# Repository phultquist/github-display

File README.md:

# GitHub Display

An ESP32-powered LED matrix display that shows your GitHub contribution graph in real-time.

## Features

- 256 LED (16x16) matrix display
- Automatic WiFi connection with captive portal setup
- Fetches data from custom API every 10 seconds
- Hard-coded Device ID: "1"
- WiFi credential reset functionality

## Initial Setup

### First Time Power-On

1. **Power on the device** - The ESP32 will boot up
2. **Wait 3 seconds** - The device will attempt to connect to WiFi (will fail on first boot)
3. **Connect to AP** - A WiFi access point named `GithubDisplay-Setup` will appear
4. **Join the network** - Connect your phone/computer to `GithubDisplay-Setup`
5. **Configure WiFi** - A captive portal should open automatically (if not, navigate to `192.168.4.1`)
6. **Enter credentials** - Select your WiFi network and enter the password
7. **Save** - Click "Save" and the device will connect to your WiFi
8. **Display starts** - The LED matrix will begin displaying your GitHub data

### What Happens Next

- WiFi credentials are **saved automatically** in the ESP32's flash memory
- On every subsequent boot, the device will **auto-connect** to your WiFi
- The display updates every **10 seconds** with fresh data from the API

## Resetting WiFi Credentials

If you need to connect to a different WiFi network or clear the stored credentials:

### Reset Procedure

1. **Press the RESET button** (don't hold any other buttons)
2. **Watch the Serial Monitor** - You'll see: `💡 Press and hold BOOT button now to clear WiFi (3 sec window)...`
3. **Quickly press and hold BOOT** - You have 3 seconds to press the BOOT button
4. **Keep holding for 2 seconds** - The status LED will blink rapidly to show progress
5. **Wait for confirmation** - After 2 seconds, you'll see 3 slow blinks = WiFi cleared!
6. **Device restarts in AP mode** - The `GithubDisplay-Setup` AP will appear again
7. **Repeat initial setup** - Follow the "First Time Power-On" steps above

### Visual Feedback

- **Rapid blinking** (during 2-second hold) = Counting down
- **3 slow blinks** = WiFi credentials successfully cleared
- **Solid LED** = Device connected and running normally

## Troubleshooting

### Device stuck in download mode (red light only)

If you accidentally held BOOT while pressing RESET, the device enters bootloader mode:

**Solution:** Simply press the RESET button once (without holding BOOT) to recover

### WiFi not connecting

1. Check that your WiFi credentials are correct
2. Make sure your WiFi network is 2.4GHz (ESP32 doesn't support 5GHz)
3. Try resetting WiFi credentials and setting up again

### Display not updating

1. Check Serial Monitor for error messages
2. Verify the device has internet access
3. Confirm the API endpoint is accessible: `https://github-display-server.vercel.app/api/1`

### Serial Monitor shows JSON parse errors

The API might be returning invalid data - check the API endpoint directly in a browser

## Hardware

- **ESP32 Development Board**
- **LED Strip:** 256 LEDs (WS2812B/NeoPixel compatible) on GPIO 5
- **Status LED:** GPIO 2 (built-in on most ESP32 boards)
- **BOOT Button:** GPIO 0 (built-in on most ESP32 boards)
- **RESET Button:** EN pin (built-in on most ESP32 boards)

## API Endpoint

The device fetches data from:
```
https://github-display-server.vercel.app/api/1
```

Expected JSON format:
```json
{
  "data": [
    [0, 255, 128, ...],  // Row 1: 16 values (0-255)
    [0, 0, 255, ...],    // Row 2: 16 values (0-255)
    // ... 16 rows total
  ]
}
```

Each value represents the green intensity (0-255) for that LED.

## Development

### Arduino IDE Setup

1. Install the Arduino IDE
2. Install ESP32 board support
3. Install required libraries:
   - Adafruit NeoPixel
   - ArduinoJson
   - WiFiManager

### Uploading Code

1. Connect ESP32 via USB
2. Select your board and port in Arduino IDE
3. Click Upload
4. Wait for compilation and upload to complete

## Configuration

All configuration is at the top of `sketch_oct14a.ino`:

```cpp
const char *API_BASE = "https://github-display-server.vercel.app/api";
const String DEVICE_ID = "1";
const int NUM_LEDS = 256;
const int STRIP_BRIGHTNESS = 5;
```

Adjust `STRIP_BRIGHTNESS` (0-255) if the display is too bright or too dim.

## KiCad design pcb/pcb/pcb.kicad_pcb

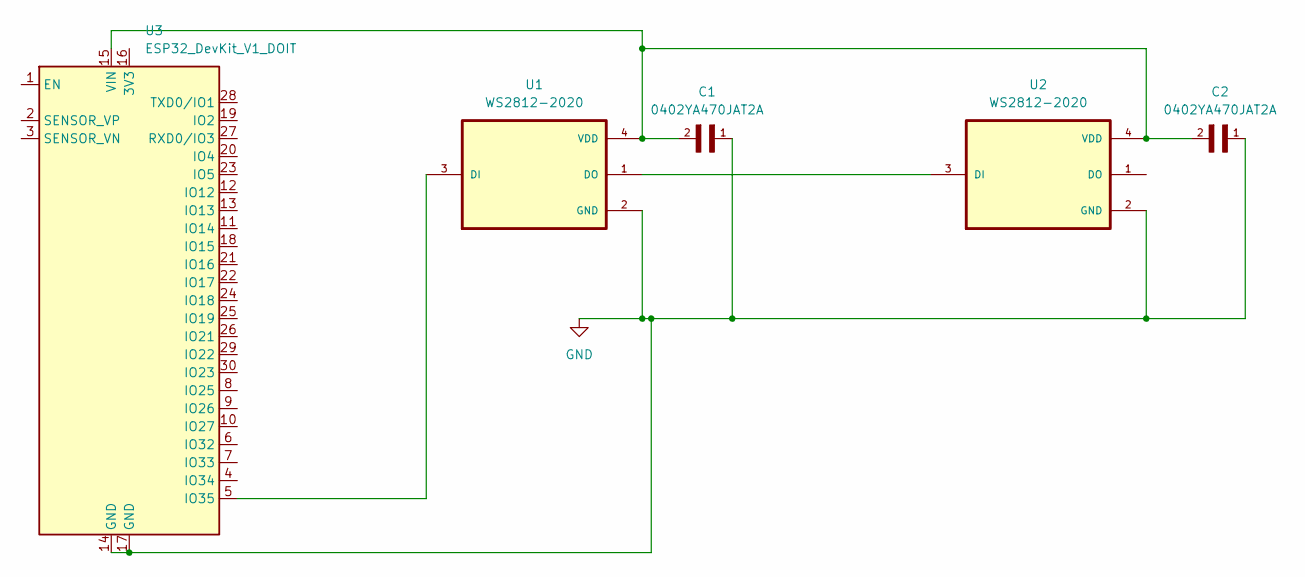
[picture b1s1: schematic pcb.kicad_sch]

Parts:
C1, C2: 0402YA470JAT2A; CAPC1005X56N
U1, U2: WS2812-2020; LED_WS2812-2020; PARTREV V1.3
U3: ESP32_DevKit_V1_DOIT; esp32_devkit_v1_doit

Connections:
GND: C1.1, C2.1, U1.2 (GND), U2.2 (GND), U3.14 (GND), U3.17 (GND)
unnamed: U1.3 (DI), U3.5 (IO35)
unnamed: U1.1 (DO), U2.3 (DI)
unnamed: C1.2, C2.2, U1.4 (VDD), U2.4 (VDD), U3.15 (VIN)

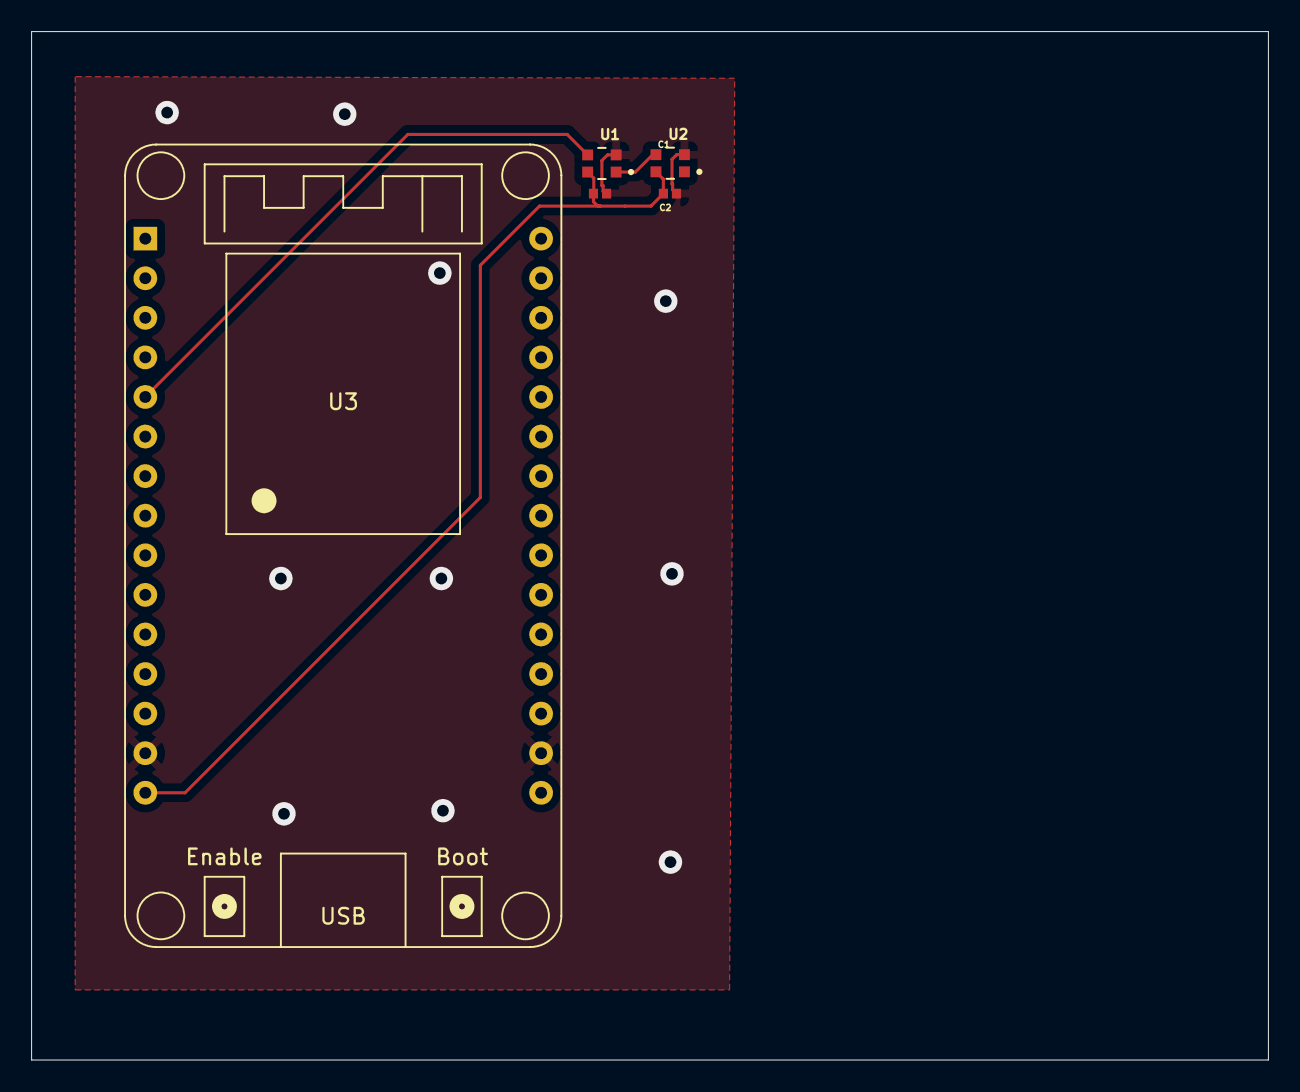
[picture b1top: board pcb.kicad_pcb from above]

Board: 2 copper layers, 79.4 x 66.0 mm, 5 parts (0 on the bottom side), 4 nets.

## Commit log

2025-10-15 made it connect to wifi with captive portal
2025-10-15 Convert server submodule to regular directory
2025-10-16 added onboarding flow
2025-10-16 created onboarding flow
2025-10-16 Hard-code Device ID and add WiFi reset functionality
    - Hard-coded DEVICE_ID to '1' and removed Preferences storage
    - Added WiFi credentials reset via BOOT button (press RESET, then hold BOOT for 2s within 3s window)
    - Removed Device ID input from WiFiManager portal since it's now hard-coded
    - Added comprehensive README with setup, reset instructions, and troubleshooting
    - WiFi credentials still auto-save and auto-connect on subsequent boots
